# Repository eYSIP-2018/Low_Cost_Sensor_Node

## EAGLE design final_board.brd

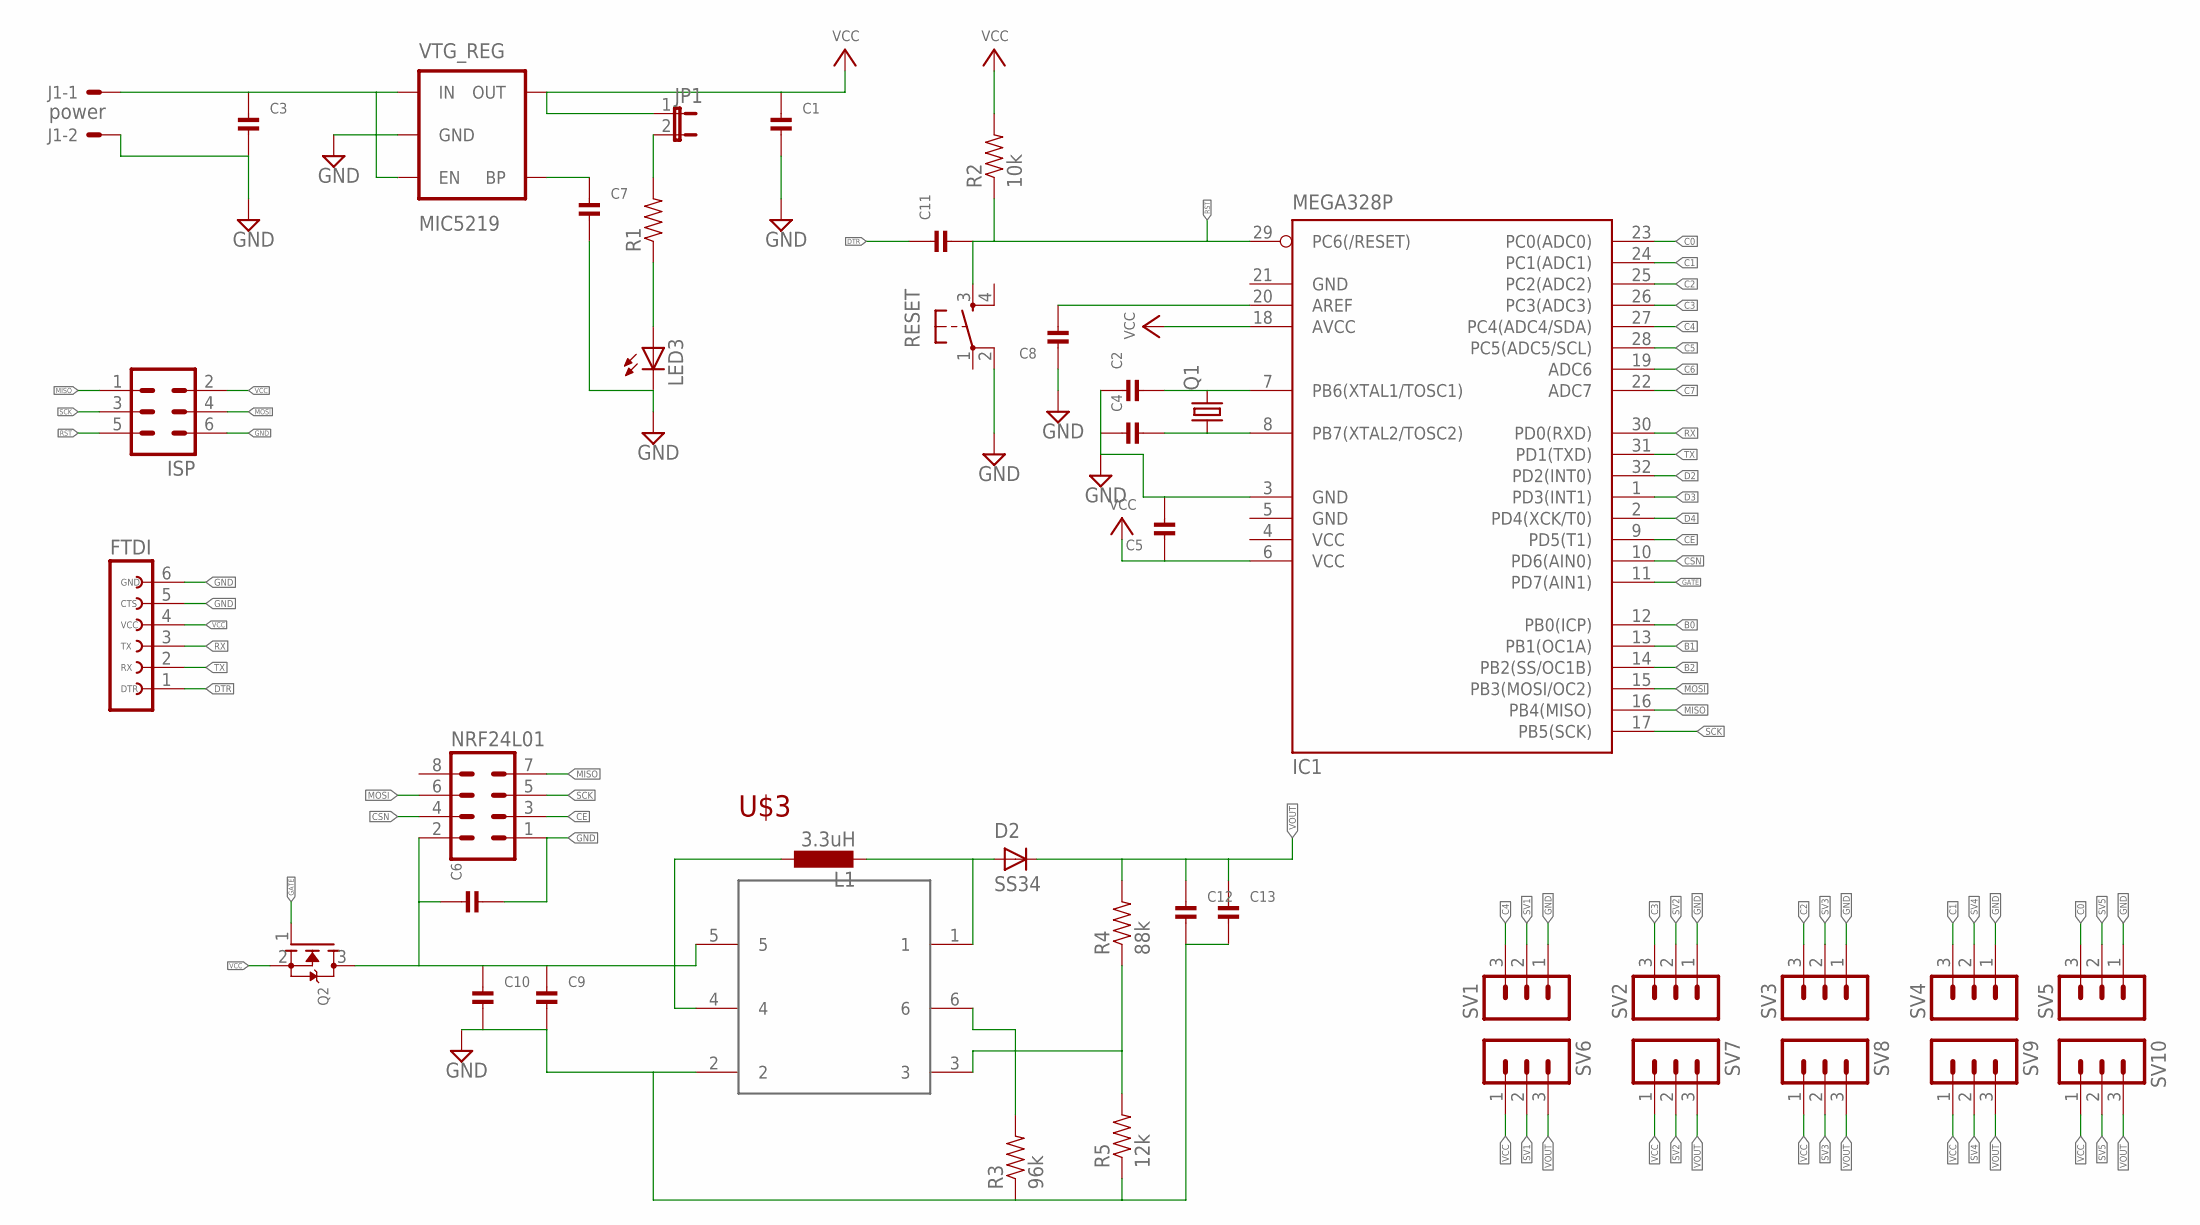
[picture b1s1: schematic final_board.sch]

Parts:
C1, C2, C3, C4, C5, C6, C7, C8, C9, C10, C11, C12, C13: CAP_CERAMIC1206; 1206
D2: SS34; SMA-DO214AC
FTDI: FE06-1; FE06
IC1: MEGA328P; TQFP32-08
ISP: MA03-2
J1: power; 6410-02
JP1: JP1E; JP1
L1: 3.3uH; L4532M
LED3: LEDSML1206; SML1206
NRF24L01: MA04-2
Q1: CRYSTALHC49U-V; HC49U-V
Q2: MOSFET-NWAVE; SOT23-W
R1: RESISTOR1206; 1206
R2: 10k; 1206
R3: 96k; 1206
R4: 88k; 1206
R5: 12k; 1206
RESET: TAC_SWITCHSMD; TACTILE_SWITCH_SMD
SV1, SV2, SV3, SV4, SV5, SV6, SV7, SV8, SV9, SV10: MA03-1
U$3: FP6291SOT23-6L; SOT23-6L
VTG_REG: MIC5219; SOT23-5

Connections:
2: C6.1, C9.1, C10.1, NRF24L01.2, Q2.3 (D), U$3.5
5V: C3.1, J1.1, VTG_REG.1 (IN), VTG_REG.3 (EN)
AREF: C8.2, IC1.20 (AREF)
B0: IC1.12 (PB0(ICP))
B1: IC1.13 (PB1(OC1A))
B2: IC1.14 (PB2(SS/OC1B))
C0: IC1.23 (PC0(ADC0)), SV5.3
C1: IC1.24 (PC1(ADC1)), SV4.3
C2: IC1.25 (PC2(ADC2)), SV3.3
C3: IC1.26 (PC3(ADC3)), SV2.3
C4: IC1.27 (PC4(ADC4/SDA)), SV1.3
C5: IC1.28 (PC5(ADC5/SCL))
C6: IC1.19 (ADC6)
C7: IC1.22 (ADC7)
CE: IC1.9 (PD5(T1)), NRF24L01.3
CSN: IC1.10 (PD6(AIN0)), NRF24L01.4
D2: IC1.32 (PD2(INT0))
D3: IC1.1 (PD3(INT1))
D4: IC1.2 (PD4(XCK/T0))
DTR: C11.1, FTDI.1
GATE: IC1.11 (PD7(AIN1)), Q2.1 (G)
GND: C1.2, C2.1, C3.2, C4.1, C5.2, C6.2, C7.2, C8.1, C9.2, C10.2, C12.2, C13.2, FTDI.5, FTDI.6, IC1.3 (GND), IC1.5 (GND), IC1.21 (GND), ISP.6, J1.2, LED3.C, NRF24L01.1, R3.1, R5.1, RESET.2, SV1.1, SV2.1, SV3.1, SV4.1, SV5.1, U$3.2, VTG_REG.2 (GND)
MISO: IC1.16 (PB4(MISO)), ISP.1, NRF24L01.7
MOSI: IC1.15 (PB3(MOSI/OC2)), ISP.4, NRF24L01.6
unnamed: C2.2, IC1.7 (PB6(XTAL1/TOSC1)), Q1.2
unnamed: C4.2, IC1.8 (PB7(XTAL2/TOSC2)), Q1.1
unnamed: JP1.2, R1.2
unnamed: LED3.A, R1.1
unnamed: C7.1, VTG_REG.4 (BP)
unnamed: L1.1, U$3.4
unnamed: R3.2, U$3.6
unnamed: D2.A, L1.2, U$3.1
unnamed: R4.1, R5.2, U$3.3
RST: C11.2, IC1.29 (PC6(/RESET)), ISP.5, R2.1, RESET.3
RX: FTDI.3, IC1.30 (PD0(RXD))
SCK: IC1.17 (PB5(SCK)), ISP.3, NRF24L01.5
SV1: SV1.2, SV6.2
SV2: SV2.2, SV7.2
SV3: SV3.2, SV8.2
SV4: SV4.2, SV9.2
SV5: SV5.2, SV10.2
TX: FTDI.2, IC1.31 (PD1(TXD))
VCC: C1.1, C5.1, FTDI.4, IC1.4 (VCC), IC1.6 (VCC), IC1.18 (AVCC), ISP.2, JP1.1, Q2.2 (S), R2.2, SV6.1, SV7.1, SV8.1, SV9.1, SV10.1, VTG_REG.5 (OUT)
VOUT: C12.1, C13.1, D2.K (C), R4.2, SV6.3, SV7.3, SV8.3, SV9.3, SV10.3

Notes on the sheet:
GND
CTS
VCC
DTR

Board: 2 copper layers, 42 parts (0 on the bottom side), 35 nets, no tracks yet.

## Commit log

2018-05-24 LPM in atmega328P
2018-05-24 arduino code for low power mode
2018-06-02 Nrf basic transmitter and recevier code
2018-06-04 Written pinmode and digital write functions in embedded C
2018-06-04 nrf trans all comment are written
2018-06-04 started writing uart code in the same file
2018-06-05 UART in Embedded with 9600 baud written
2018-06-05 Codes for 2 transmitter and one receiver in star network with data diffrentation
2018-06-06 Progress presenatation 1
2018-06-06 progress presentation 1
2018-06-06 Progress Presentation
2018-06-07 Final pcb design
2018-06-07 timero and UART ,LED BLINK in EMBEDDED
2018-06-07 UART and blink issue solved
2018-06-08 mesh_network simple transmission using 3 nodes
2018-06-10 PCB_design
2018-06-10 final_pcb_board
2018-06-11 delay using timer0 in embedded C
2018-06-11 RF24 library project in ATMEL STUDIO7 succesfully compiled
2018-06-12 data differentiate
2018-06-13 RF receiver code SPI library modified in atmel
2018-06-15 RF24 project in Atmel with own SPI library
2018-06-16 Both transmitter and receiver code in one cpp project
2018-06-19 settings for 1 sec time out added
2018-06-19 multitrasmitter code for 3 tx in ATMEL
2018-06-21 updated by NiTHiN
2018-06-21 Progress prasiontation_2
2018-06-21 progress presentation 2
2018-06-21 tx and rx with dutycyling in power down and data diffrentiation
2018-06-21 new function for printing byte added
2018-06-21 function for getting data in byte format is added
2018-06-26 gateway implemenation with hanshaking and post request
2018-06-26 esp code for gateway
2018-06-27 ESP 8 data on one channel
2018-06-27 Serial communication between atmegand esp32
2018-06-29 proper handshakimg with esp32 along with 4 node data
2018-06-29 NRF recevier and esp communication merged
2018-06-29 send serial data to gateway updated by NiTHiN
2018-06-29 multidata uploaded to 2 different channels Updated by NiTHiN
2018-07-01 ESP Final working
2018-07-23 Chnages Made before final demo
2018-07-23 folder for all SCHEMATIC FILES
2018-07-23 Workng code seperate directory
2018-07-25 Repo cleaned made diffrent folders
2018-08-05 Final report and code documents added
2018-08-05 minor changes added
2018-08-05 cleaned repo to keep documents at one place
2018-08-05 Progress presentation 1 and 2 cleaned
2018-08-05 final WORKING code well commented and added functions

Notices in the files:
parts and their libraries:
SparkFun: Licensing: CC v3.0 Share-Alike You are welcome to use this library for commercial purposes.
